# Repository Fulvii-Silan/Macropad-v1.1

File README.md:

# Macropad-v1.1
This repo will be sent to HackClub. This attempt is much better than the first one!
Actually this project name is Sledge. I don't know why I named the repo "Macropad-v1.1"

Sledge features 6 keys (one of them is 1.75mm long), 1 rotary encoder, and 1 OLED screen.

## CAD model
Made in Fusion360

This case consists of 3 printed parts - Bottom, plate, and the top cover. Apart from these, I've made cap for the rotary encoder, as I thought it would be boring and somewhat uncomfortable to use it as it is.

## PCB and Schematics
Made in KiCAD

## BOM
- 1x PCB
- 1x XIAO RP2040
- 1x EC11 Rotary Encoder
- 7x 1N4148 Diodes
- 6x SW Cherry MX Switches
- 1x 0.91" 128x32 OLED Display
- 4x M3x16mm Screws
- 4x M3x5mm x 4mm Heatset Inserts
- 1x Case (Bottom, Plate, Top - all are different components. Are White, red, and white, respectively)
- 1x Knob Cap
- 5x Keycaps 1u size
- 1x Keycap 1.75u size

[bom.csv](https://github.com/user-attachments/files/24339512/bom.csv)
(OLED screen itself was not included in this file)

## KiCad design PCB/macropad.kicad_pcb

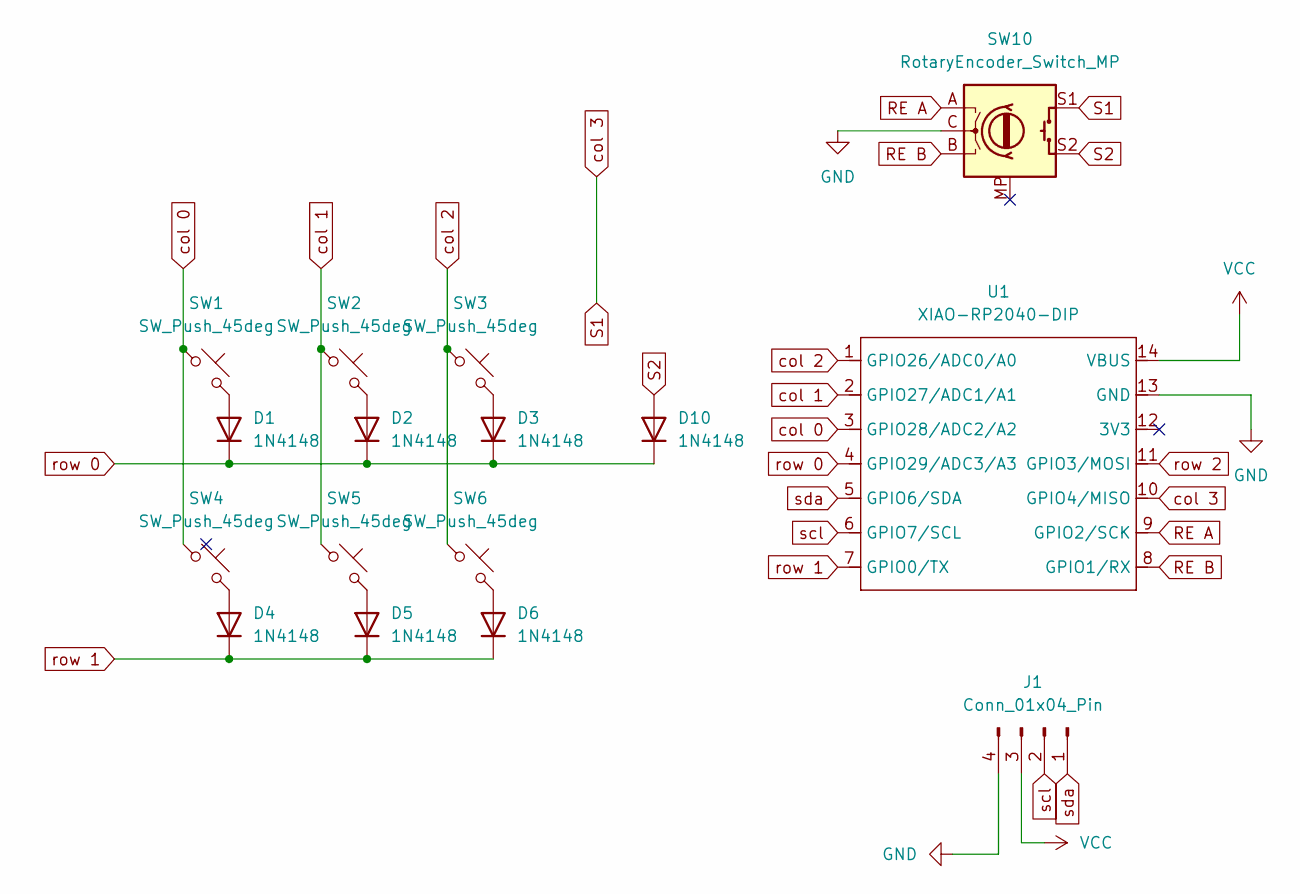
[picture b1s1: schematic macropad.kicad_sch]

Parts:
D1, D2, D3, D4, D5, D6, D10: 1N4148; D_DO-35_SOD27_P7.62mm_Horizontal
J1: Conn_01x04_Pin; PinHeader_1x04_P2.54mm_Vertical
SW1, SW2, SW3, SW4, SW5: SW_Push_45deg; SW_Cherry_MX_1.00u_PCB
SW6: SW_Push_45deg; SW_Cherry_MX_1.75u_PCB
SW10: RotaryEncoder_Switch_MP; RotaryEncoder_Alps_EC11E-Switch_Vertical_H20mm
U1: XIAO-RP2040-DIP

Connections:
GND: J1.4, SW10.C, U1.13 (GND)
unnamed: D1.2 (A), SW1.2
unnamed: D2.2 (A), SW2.2
unnamed: D3.2 (A), SW3.2
unnamed: D4.2 (A), SW4.2
unnamed: D5.2 (A), SW5.2
unnamed: D6.2 (A), SW6.2
RE A: SW10.A, U1.9 (GPIO2/SCK)
RE B: SW10.B, U1.8 (GPIO1/RX)
S1: SW10.S1, U1.10 (GPIO4/MISO)
S2: D10.2 (A), SW10.S2
VCC: J1.3, U1.14 (VBUS)
col 0: SW1.1, SW4.1, U1.3 (GPIO28/ADC2/A2)
col 1: SW2.1, SW5.1, U1.2 (GPIO27/ADC1/A1)
col 2: SW3.1, SW6.1, U1.1 (GPIO26/ADC0/A0)
row 0: D1.1 (K), D2.1 (K), D3.1 (K), D10.1 (K), U1.4 (GPIO29/ADC3/A3)
row 1: D4.1 (K), D5.1 (K), D6.1 (K), U1.7 (GPIO0/TX)
row 2: U1.11 (GPIO3/MOSI)
scl: J1.2, U1.6 (GPIO7/SCL)
sda: J1.1, U1.5 (GPIO6/SDA)

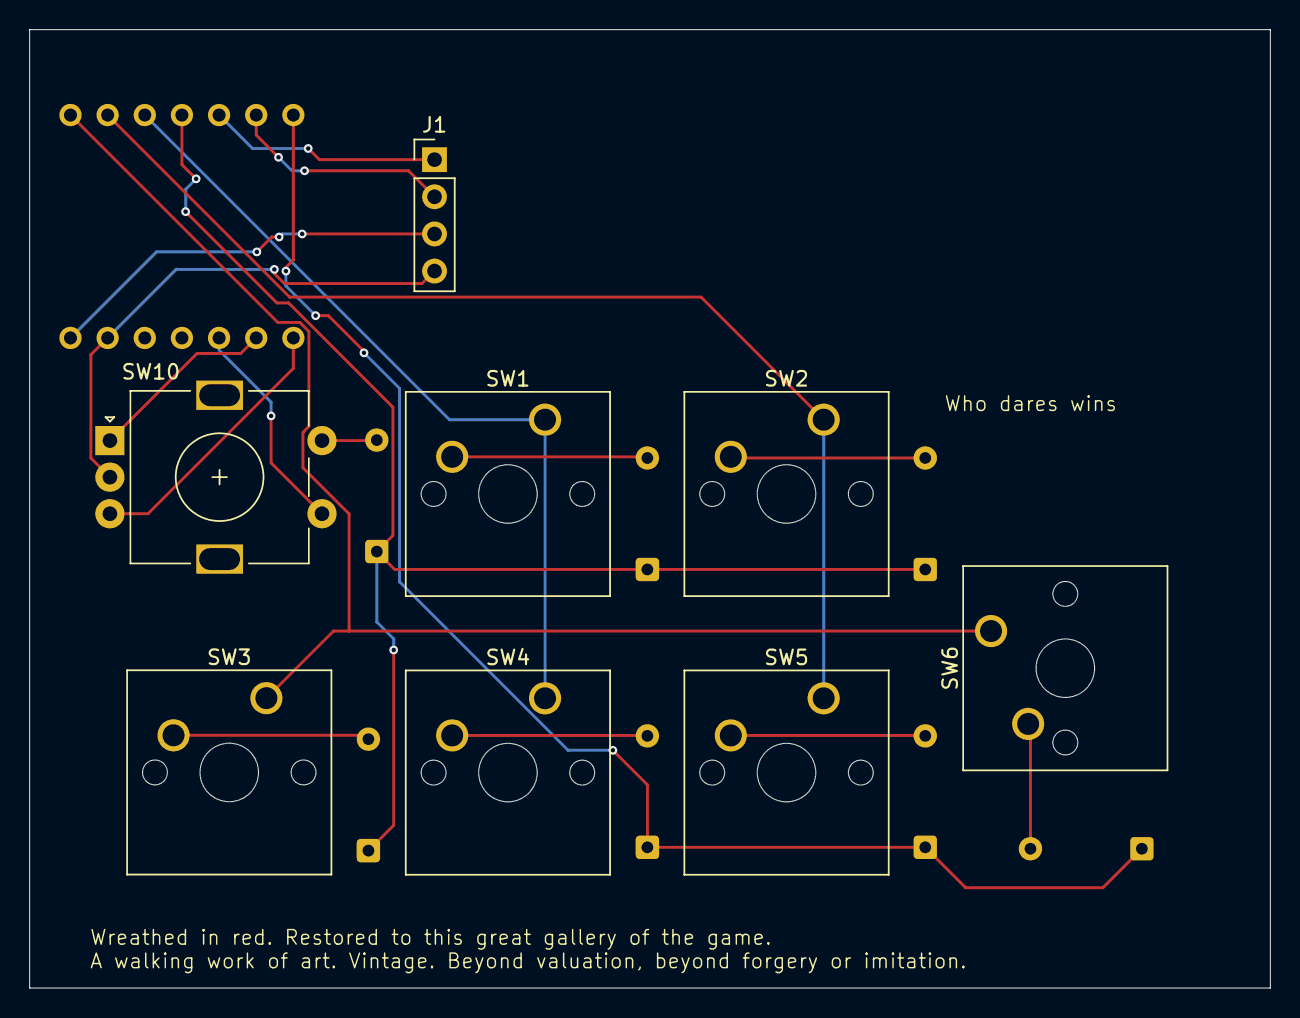
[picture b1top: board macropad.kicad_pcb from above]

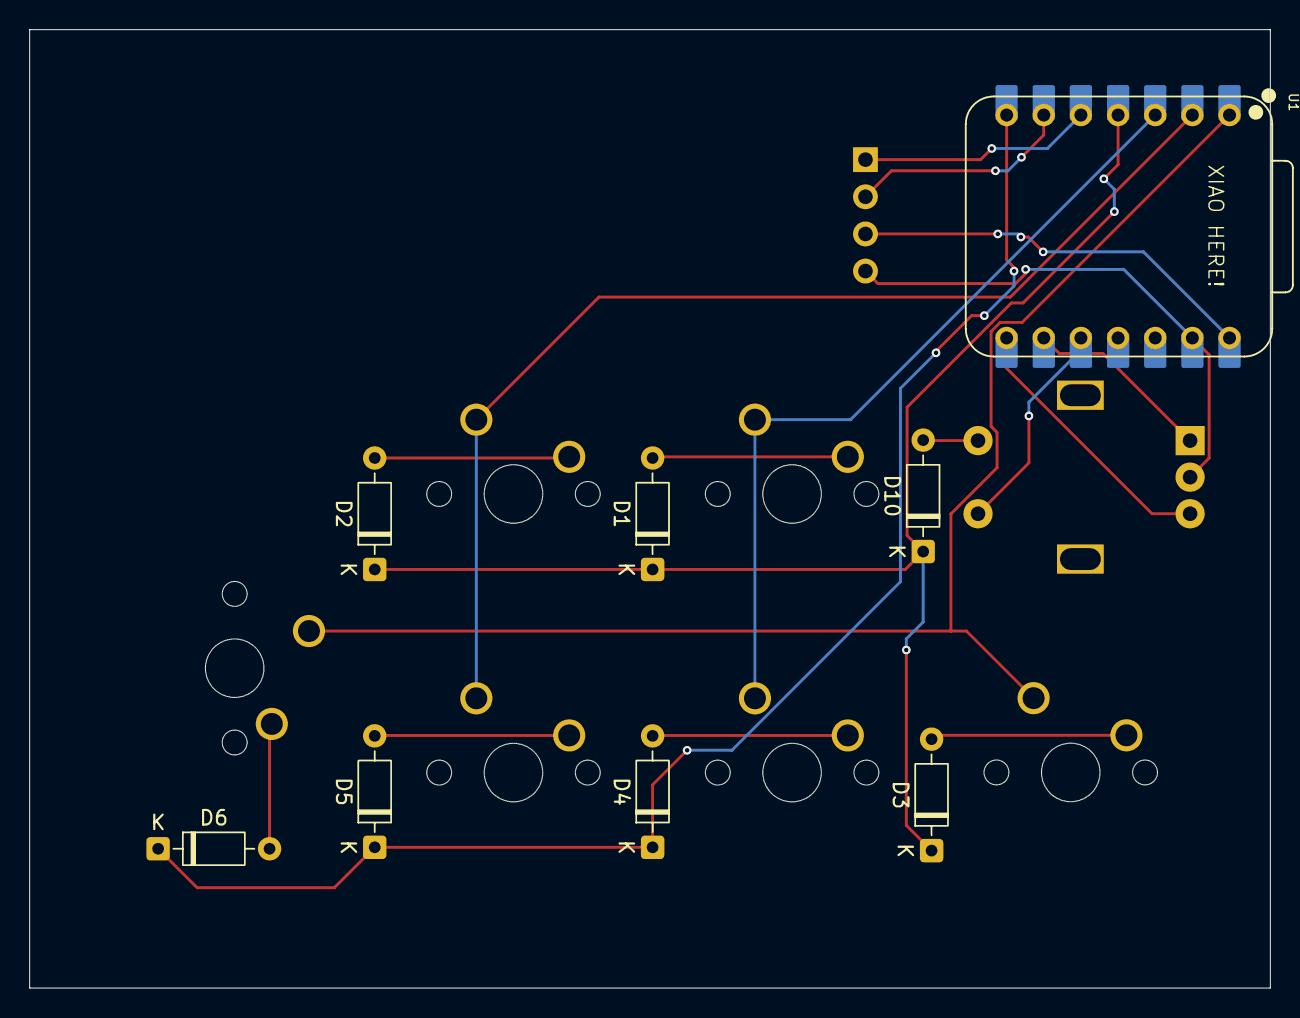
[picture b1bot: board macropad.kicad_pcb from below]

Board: 2 copper layers, 84.8 x 65.5 mm, 16 parts (8 on the bottom side), 19 nets.

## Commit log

2025-12-23 Create fd
2025-12-23 Create fa
